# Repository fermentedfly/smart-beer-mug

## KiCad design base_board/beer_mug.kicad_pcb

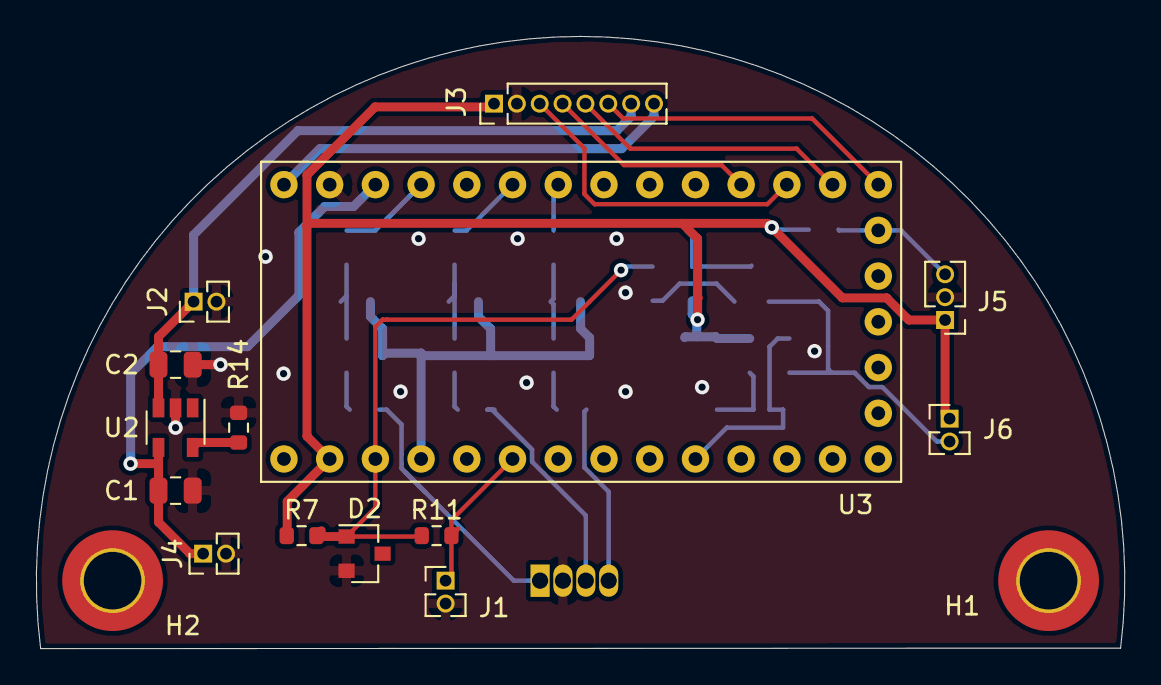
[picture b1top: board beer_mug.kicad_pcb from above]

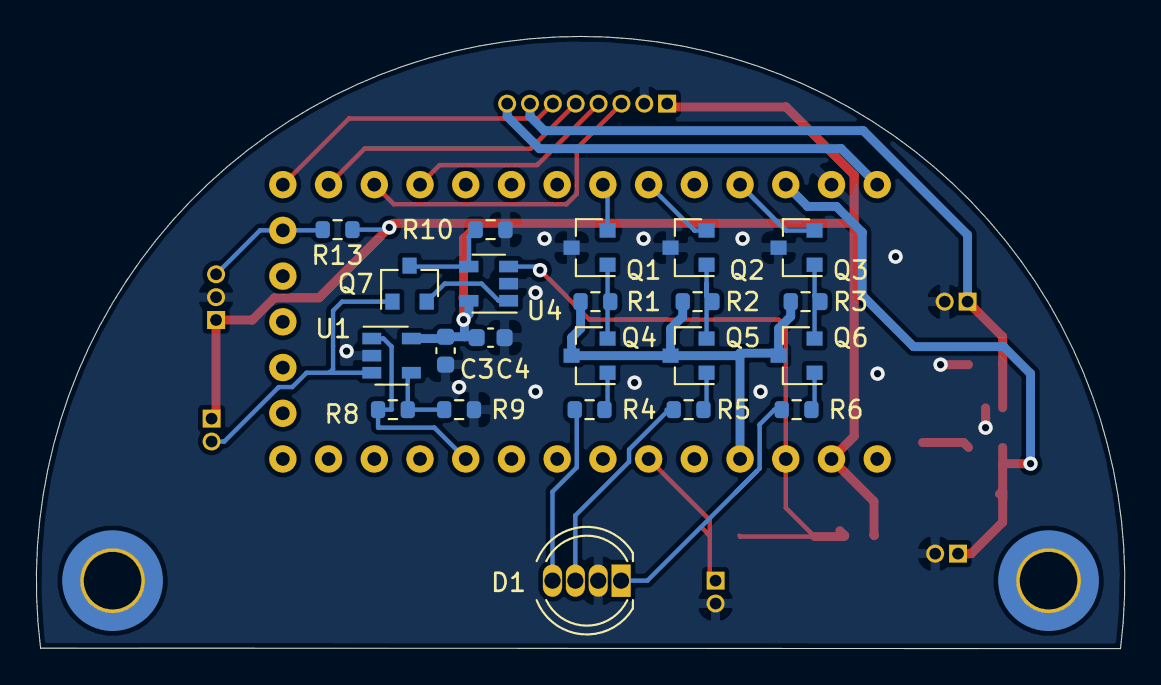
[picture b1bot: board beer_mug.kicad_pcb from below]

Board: 2 copper layers, 60.5 x 34.0 mm, 38 parts (22 on the bottom side), 31 nets.

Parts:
C1, C2: 4u7; C_0805_2012Metric
C3, C4: 100n; C_0603_1608Metric
D1: LED_RAGB; LED_D5.0mm-4_RGB
D2: LM4040CIM3-3.0; SOT-23
H1, H2: MountingHole; MountingHole_3.2mm_M3_DIN965_Pad_TopBottom
J1, J2, J4, J6: Conn_01x02; PinHeader_1x02_P1.27mm_Vertical
J3: Conn_01x08; PinHeader_1x08_P1.27mm_Vertical
J5: Conn_01x03; PinHeader_1x03_P1.27mm_Vertical
Q1, Q2, Q3, Q7: Q_NMOS_DGS; SOT-23
Q4, Q5, Q6: Q_PMOS_DGS; SOT-23
R1, R2, R3, R4, R5, R6, R8, R9, R10, R11, R13, R14: R; R_0603_1608Metric
R7: 300; R_0603_1608Metric
U1, U4: OPA322; SOT-23-5
U2: MCP73832-2-OT; SOT-23-5
U3: Itsy-Bitsy-M0; adafruit-itsy-bitsy-m0

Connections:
+3V3: C3.1, C4.1, J3.1, J5.1, J6.1, R7.1, R13.1, U1.5, U3.2, U4.5
+BATT: C2.1, J2.1, J3.7, U2.3
/1Wire: J5.3, R13.2, U3.19
/A1: J1.1, R11.2, U3.6
/A5: R8.1, U1.1, U3.10
/AREF: D2.1, R7.2, R11.1, U3.3, U4.3
/Blue: Q3.2, U3.30
/Blue_Driver: Q3.1, Q6.2, R3.2
/Button_1: J3.5, U3.21
/Button_2: J3.6, U3.20
/FLUID_SENSE-: J6.2, Q7.1, U1.3
/Green: Q2.2, U3.28
/Green_Driver: Q2.1, Q5.2, R2.2
/I2C_SCL: J3.4, U3.23
/I2C_SDA: J3.3, U3.22
/Red: Q1.2, U3.27
/Red_Driver: Q1.1, Q4.2, R1.2
/VBAT_SWITCHED: J3.8, U3.33
GND: C1.2, C2.2, C3.2, C4.2, D1.2, D2.2, J1.2, J2.2, J3.2, J4.2, J5.2, Q1.3, Q2.3, Q3.3, R9.2, R10.2, R14.2, U1.2, U2.2, U3.32, U4.2
unnamed: D1.1, R6.2
unnamed: D1.3, R5.2
unnamed: D1.4, R4.2
unnamed: Q4.1, R4.1
unnamed: Q5.1, R5.1
unnamed: Q6.1, R6.1
unnamed: Q7.2, U4.1
unnamed: Q7.3, R10.1, U4.4
unnamed: R8.2, R9.1, U1.4
unnamed: R14.1, U2.5
VBUS: C1.1, J4.1, U2.4, U3.31
VCC: Q4.3, Q5.3, Q6.3, R1.1, R2.1, R3.1, U3.4

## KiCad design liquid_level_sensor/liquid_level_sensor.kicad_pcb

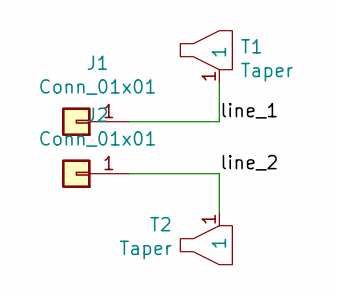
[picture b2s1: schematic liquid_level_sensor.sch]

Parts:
J1, J2: Conn_01x01; pad
T1, T2: Taper; uwT1.00_0.50_2.00_2.00_4.00

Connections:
/line_1: J1.1, T1.1
/line_2: J2.1, T2.1

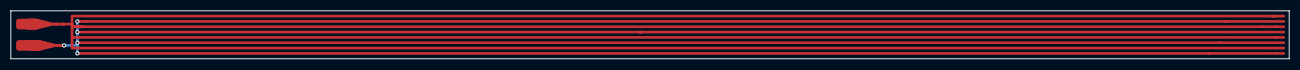
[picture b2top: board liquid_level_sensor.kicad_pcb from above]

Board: 2 copper layers, 240.0 x 9.0 mm, 4 parts (0 on the bottom side), 2 nets.

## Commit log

2021-08-28 added base board schematics (wip)
2021-08-28 added liquid level sensor
2021-08-28 added demo itsy bitsy project
2021-08-30 updated schematic
2021-08-30 fixed folder name
2021-08-30 added ds18b20 test, added tasks
2021-09-08 pcb update
